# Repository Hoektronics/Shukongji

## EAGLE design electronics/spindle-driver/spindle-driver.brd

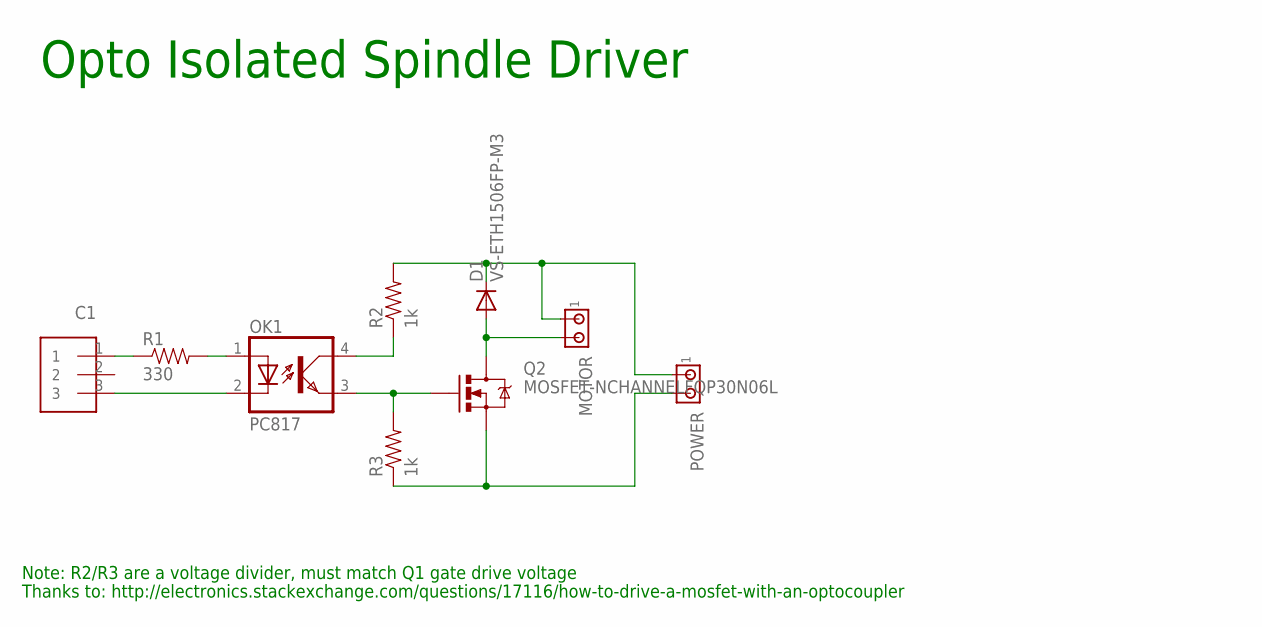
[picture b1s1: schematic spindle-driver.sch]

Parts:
C1: CONN-3XH-3; XH-3
D1: VS-ETH1506FP-M3; SMB
MOTOR: MTA02-156; 1X2MTA
OK1: PC817; DIL04
POWER: MTA02-156; 1X2MTA
Q2: MOSFET-NCHANNELFQP30N06L; TO220V
R1: 330; 0805-RC
R2, R3: 1k; 0805-RC

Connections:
unnamed: C1.3, OK1.2 (C)
unnamed: OK1.1 (A), R1.2
unnamed: C1.1, R1.1
unnamed: D1.C, MOTOR.1, POWER.1, R2.2
unnamed: OK1.4 (COL), R2.1
unnamed: OK1.3 (EMIT), Q2.1 (G), R3.2
unnamed: POWER.2, Q2.3 (S), R3.1
unnamed: D1.A, MOTOR.2, Q2.2 (D)

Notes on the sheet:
Thanks to: http://electronics.stackexchange.com/questions/17116/how-to-drive-a-mosfet-with-an-optocoupler
Note: R2/R3 are a voltage divider, must match Q1 gate drive voltage
Opto Isolated Spindle Driver

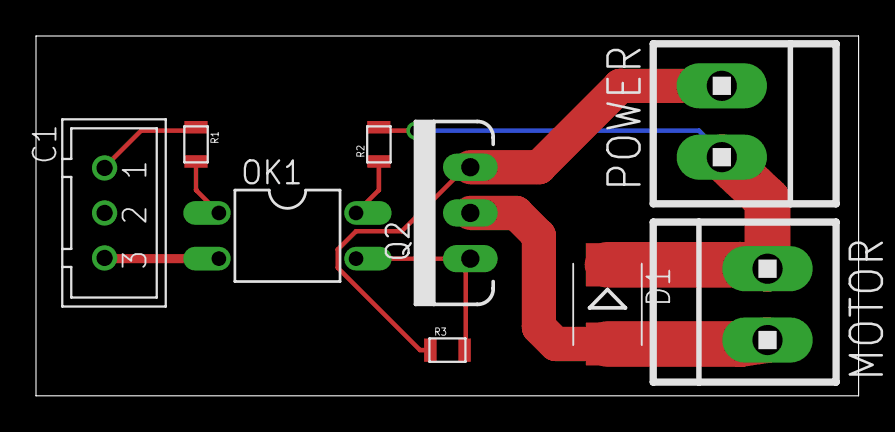
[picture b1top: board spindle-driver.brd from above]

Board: 2 copper layers, 45.7 x 20.0 mm, 9 parts (0 on the bottom side), 8 nets.

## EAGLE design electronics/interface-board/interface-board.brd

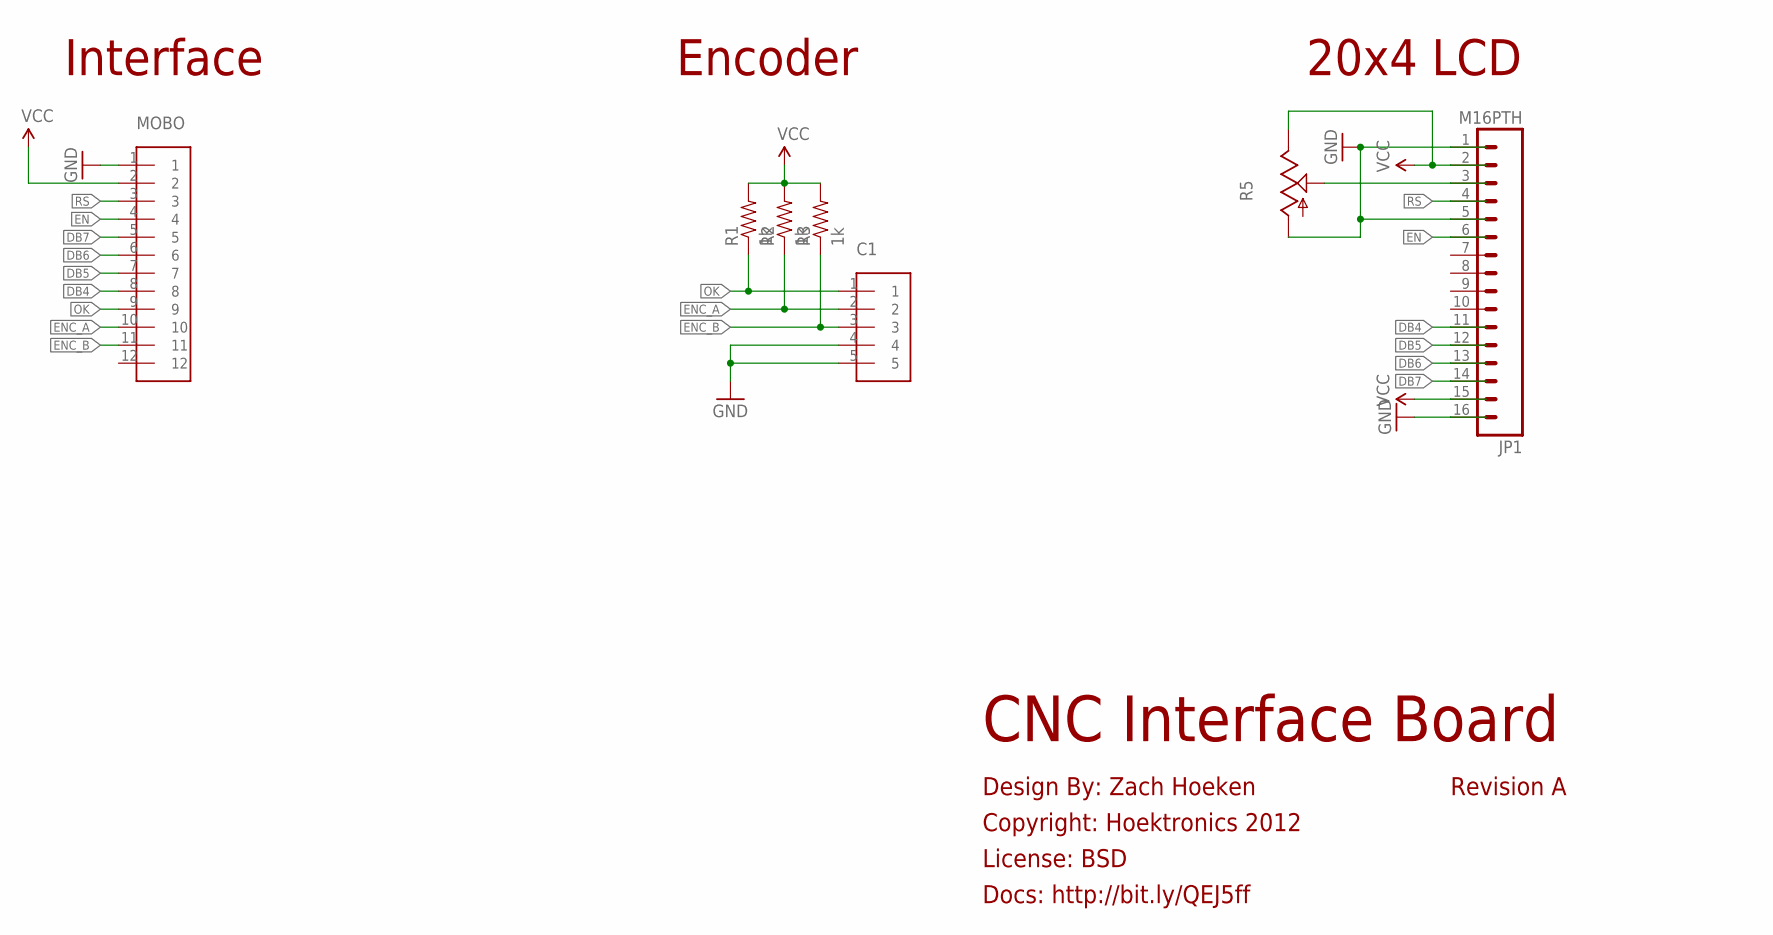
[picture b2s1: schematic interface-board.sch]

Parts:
C1: CONN-5; XH-5
JP1: M16PTH; 1X16
MOBO: CONN-12; XH-12
R1, R2, R3: 1k; 0805-RC
R5: TRIM_US-B25P; B25P

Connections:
DB4: JP1.11, MOBO.8
DB5: JP1.12, MOBO.7
DB6: JP1.13, MOBO.6
DB7: JP1.14, MOBO.5
EN: JP1.6, MOBO.4
ENC_A: C1.2, MOBO.10, R2.1
ENC_B: C1.3, MOBO.11, R3.1
GND: C1.4, C1.5, JP1.1, JP1.5, JP1.16, MOBO.1, R5.A
unnamed: JP1.3, R5.S
OK: C1.1, MOBO.9, R1.1
RS: JP1.4, MOBO.3
VCC: JP1.2, JP1.15, MOBO.2, R1.2, R2.2, R3.2, R5.E

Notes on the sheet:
CNC Interface Board
Docs: http://bit.ly/QEJ5ff
License: BSD
Copyright: Hoektronics 2012
Design By: Zach Hoeken
20x4 LCD
Revision A
Interface
Encoder

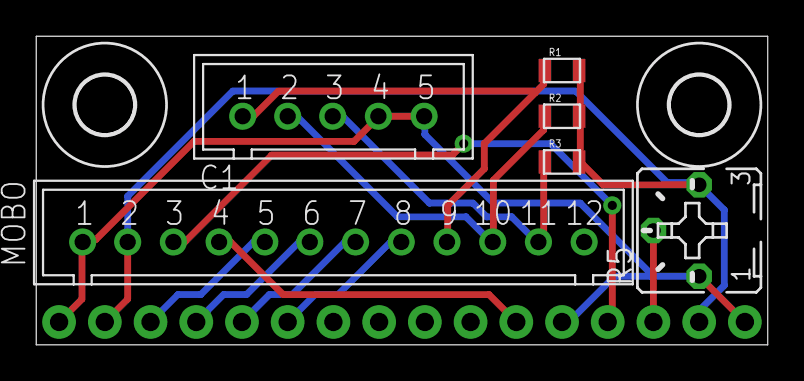
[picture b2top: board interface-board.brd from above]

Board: 2 copper layers, 40.6 x 17.1 mm, 9 parts (1 on the bottom side), 12 nets.

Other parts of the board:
U$1, U$2: 3,2

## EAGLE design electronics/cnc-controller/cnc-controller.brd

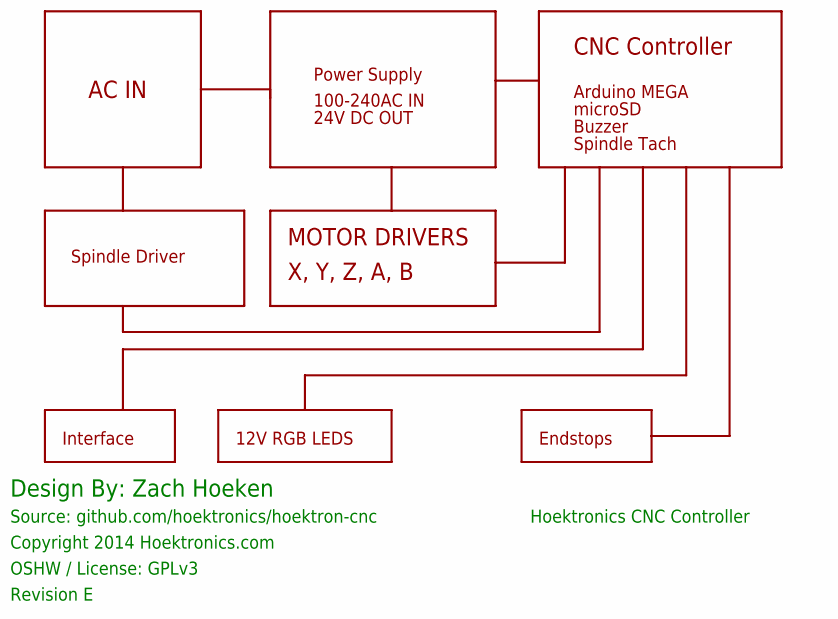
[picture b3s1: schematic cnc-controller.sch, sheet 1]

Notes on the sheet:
Hoektronics CNC Controller
Design By: Zach Hoeken
Source: github.com/hoektronics/hoektron-cnc
Copyright 2014 Hoektronics.com
Power Supply
X, Y, Z, A, B
CNC Controller
microSD
Endstops
Buzzer
OSHW / License: GPLv3
12V RGB LEDS
24V DC OUT
Interface
Revision E
Arduino MEGA
100-240AC IN
AC IN
MOTOR DRIVERS
Spindle Tach
Spindle Driver

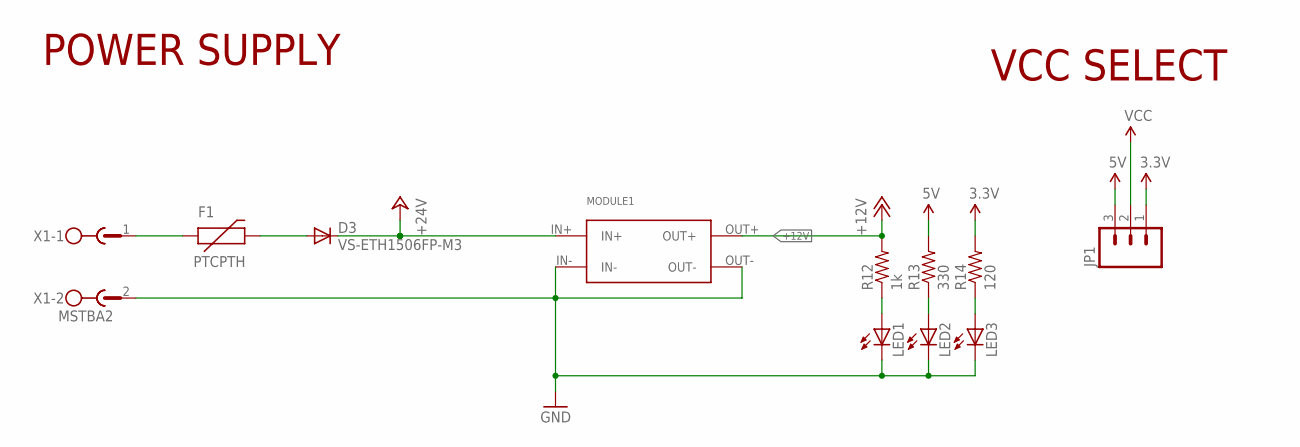
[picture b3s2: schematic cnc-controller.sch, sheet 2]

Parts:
D3: VS-ETH1506FP-M3; SMB
F1: PTCPTH; PTC
JP1: M03PTH; 1X03
LED1, LED2, LED3: LED0805; 0805-LED
MODULE1: DC-DC-CONVERTER; DC-DC-MODULE
R12: 1k; 0603-RC
R13: 330; 0603-RC
R14: 120; 0603-RC
X1: MSTBA2

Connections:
3.3V: JP1.1, R14.2; also elsewhere on the board
5V: JP1.3, R13.2; also elsewhere on the board
+12V: MODULE1.OUT+, R12.2; also elsewhere on the board
+24V: D3.C, MODULE1.IN+
GND: LED1.C, LED2.C, LED3.C, MODULE1.IN-, MODULE1.OUT-, X1.2; also elsewhere on the board
unnamed: LED1.A, R12.1
unnamed: D3.A, F1.P$2 (2)
unnamed: LED2.A, R13.1
unnamed: LED3.A, R14.1
PRE24: F1.P$1 (1), X1.1
VCC: JP1.2; also elsewhere on the board

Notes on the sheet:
POWER SUPPLY
VCC SELECT

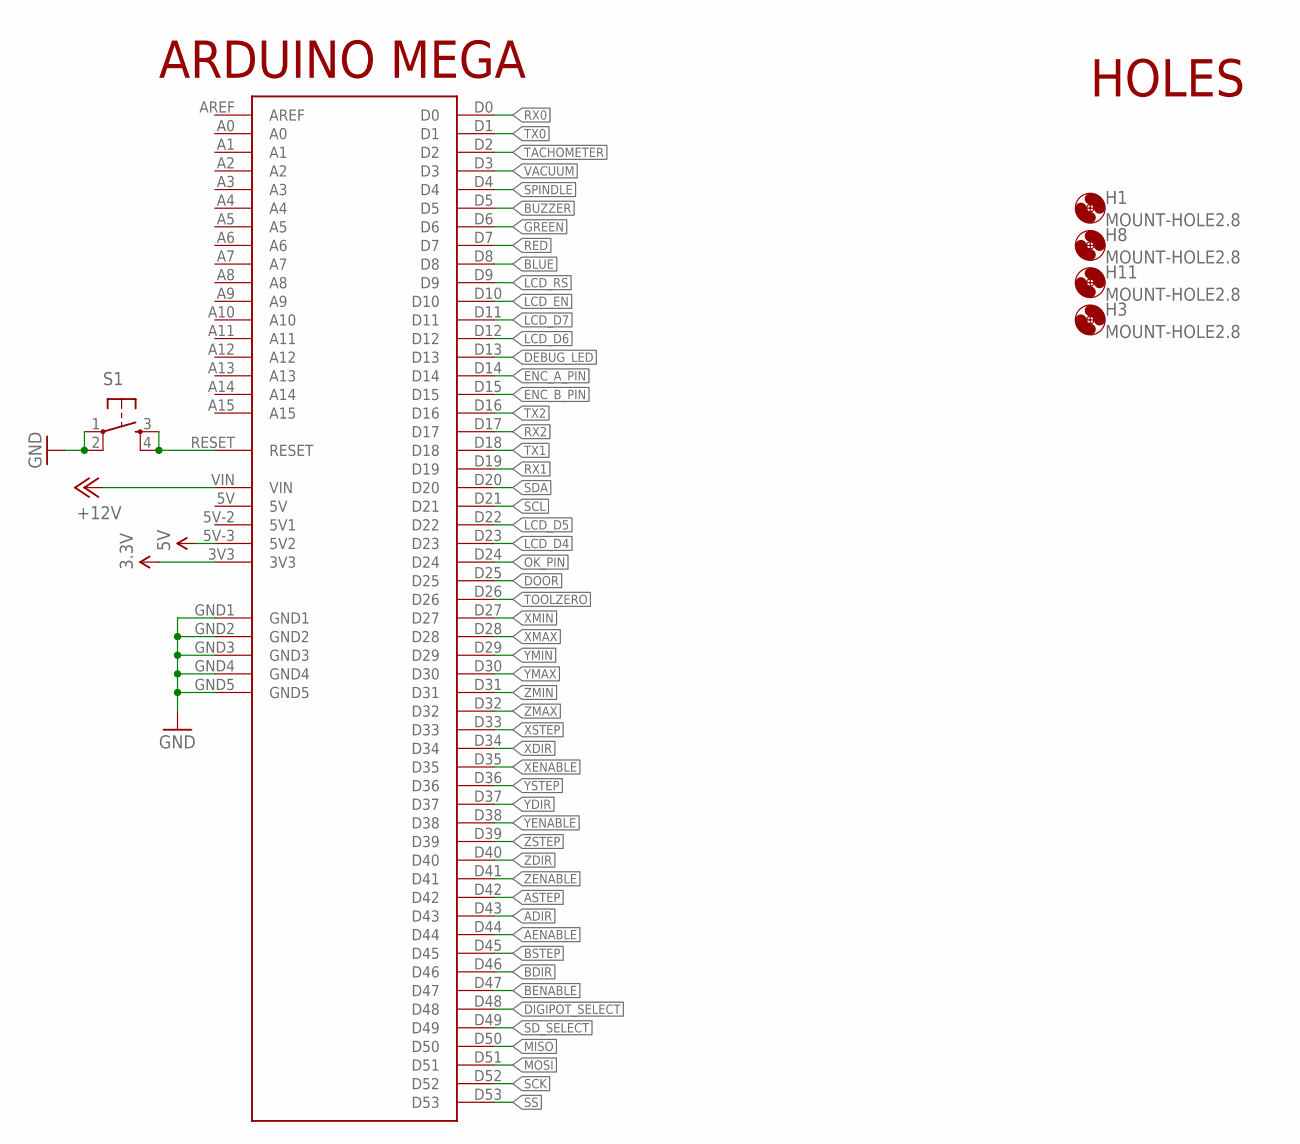
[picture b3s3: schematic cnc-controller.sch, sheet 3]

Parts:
H1, H3, H8, H11: MOUNT-HOLE2.8; 2,8
S1: TAC_SWITCHSMD; TACTILE_SWITCH_SMD
U$1: ARDUINO-MEGA

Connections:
3.3V: U$1.3V3; also elsewhere on the board
5V: U$1.5V-3 (5V2); also elsewhere on the board
+12V: U$1.VIN; also elsewhere on the board
ADIR: U$1.D43; also elsewhere on the board
AENABLE: U$1.D44; also elsewhere on the board
ASTEP: U$1.D42; also elsewhere on the board
BDIR: U$1.D46; also elsewhere on the board
BENABLE: U$1.D47; also elsewhere on the board
BLUE: U$1.D8; also elsewhere on the board
BSTEP: U$1.D45; also elsewhere on the board
BUZZER: U$1.D5; also elsewhere on the board
DEBUG_LED: U$1.D13
DIGIPOT_SELECT: U$1.D48
DOOR: U$1.D25; also elsewhere on the board
ENC_A_PIN: U$1.D14; also elsewhere on the board
ENC_B_PIN: U$1.D15; also elsewhere on the board
GND: S1.1, S1.2, U$1.GND1, U$1.GND2, U$1.GND3, U$1.GND4, U$1.GND5; also elsewhere on the board
GREEN: U$1.D6; also elsewhere on the board
LCD_D4: U$1.D23; also elsewhere on the board
LCD_D5: U$1.D22; also elsewhere on the board
LCD_D6: U$1.D12; also elsewhere on the board
LCD_D7: U$1.D11; also elsewhere on the board
LCD_EN: U$1.D10; also elsewhere on the board
LCD_RS: U$1.D9; also elsewhere on the board
MISO: U$1.D50; also elsewhere on the board
MOSI: U$1.D51; also elsewhere on the board
unnamed: S1.3, S1.4, U$1.RESET
OK_PIN: U$1.D24; also elsewhere on the board
RED: U$1.D7; also elsewhere on the board
RX0: U$1.D0
RX1: U$1.D19; also elsewhere on the board
RX2: U$1.D17; also elsewhere on the board
SCK: U$1.D52; also elsewhere on the board
SCL: U$1.D21; also elsewhere on the board
SDA: U$1.D20; also elsewhere on the board
SD_SELECT: U$1.D49; also elsewhere on the board
SPINDLE: U$1.D4; also elsewhere on the board
SS: U$1.D53; also elsewhere on the board
TACHOMETER: U$1.D2; also elsewhere on the board
TOOLZERO: U$1.D26; also elsewhere on the board
TX0: U$1.D1
TX1: U$1.D18; also elsewhere on the board
TX2: U$1.D16; also elsewhere on the board
VACUUM: U$1.D3; also elsewhere on the board
XDIR: U$1.D34; also elsewhere on the board
XENABLE: U$1.D35; also elsewhere on the board
XMAX: U$1.D28; also elsewhere on the board
XMIN: U$1.D27; also elsewhere on the board
XSTEP: U$1.D33; also elsewhere on the board
YDIR: U$1.D37; also elsewhere on the board
YENABLE: U$1.D38; also elsewhere on the board
YMAX: U$1.D30; also elsewhere on the board
YMIN: U$1.D29; also elsewhere on the board
YSTEP: U$1.D36; also elsewhere on the board
ZDIR: U$1.D40; also elsewhere on the board
ZENABLE: U$1.D41; also elsewhere on the board
ZMAX: U$1.D32; also elsewhere on the board
ZMIN: U$1.D31; also elsewhere on the board
ZSTEP: U$1.D39; also elsewhere on the board

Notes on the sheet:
ARDUINO MEGA
HOLES

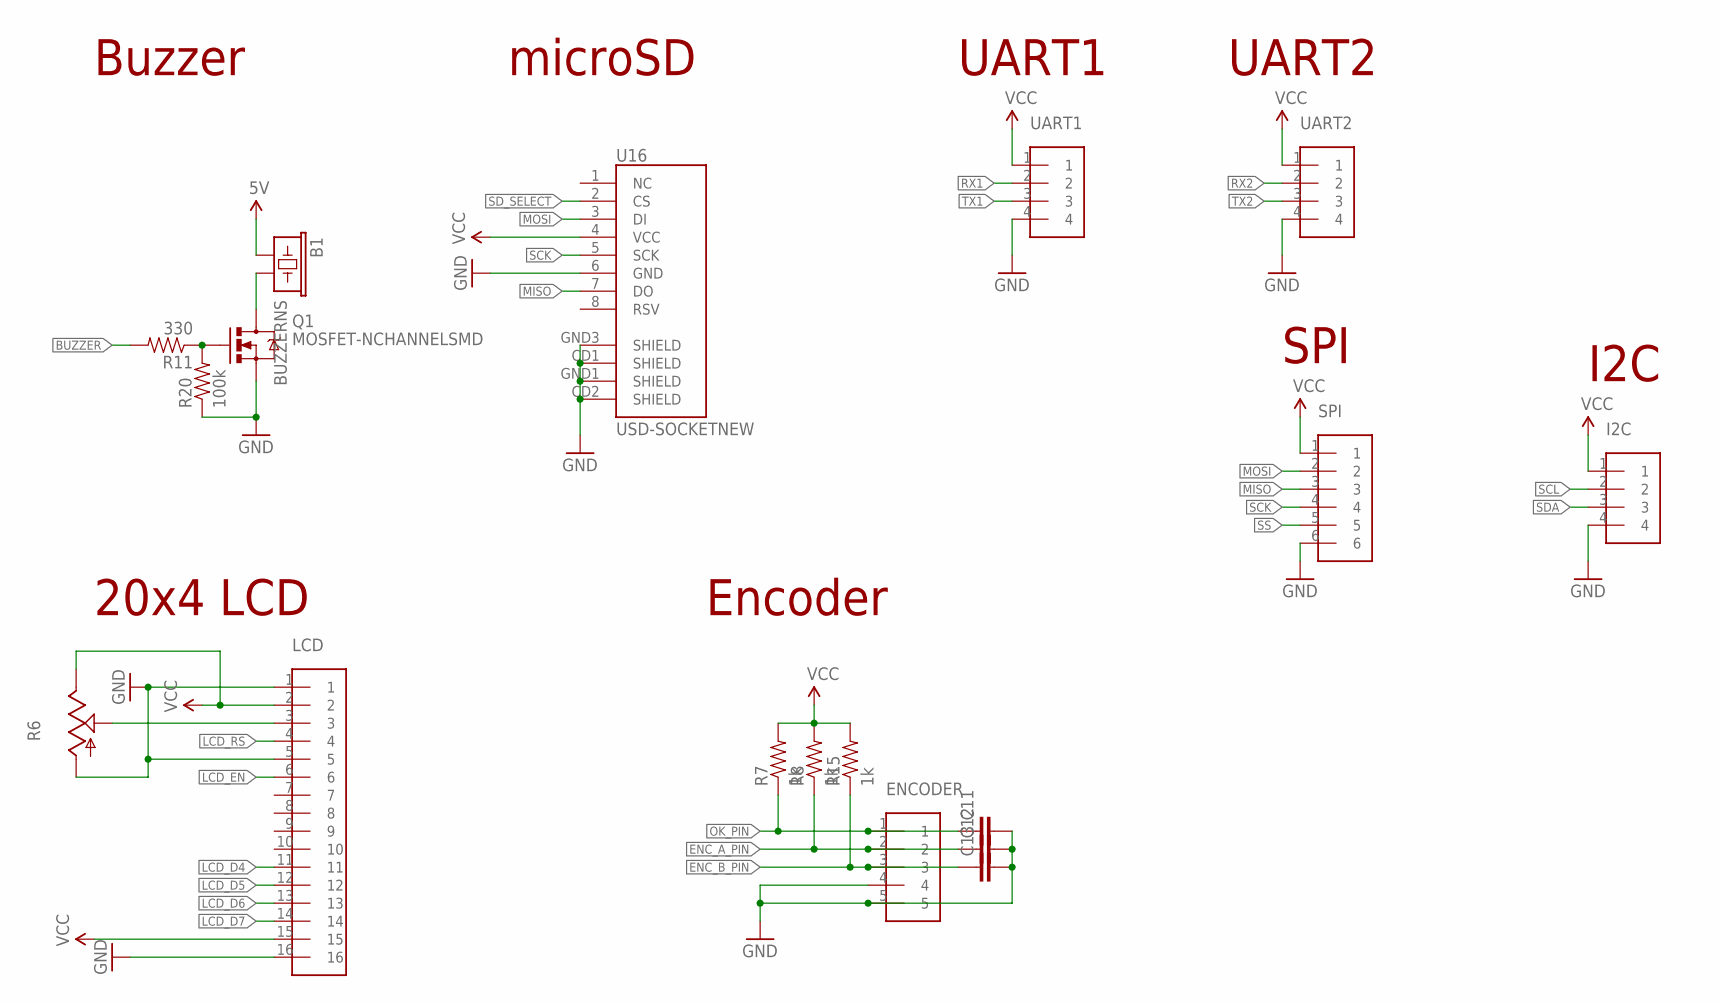
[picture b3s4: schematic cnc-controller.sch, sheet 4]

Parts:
B1: BUZZERNS; BUZZER-12MM-NS
C11, C12, C13: CAPACITOR0805; 0805-RC
ENCODER: CONN-5; XH-5
I2C: CONN-4; XH-4
LCD: CONN-16; XH-16
Q1: MOSFET-NCHANNELSMD; SOT23-3
R6: TRIM_US-B25P; B25P
R7, R8, R15: 1k; 0805-RC
R11: 330; 0603-RC
R20: 100k; 0603-RC
SPI: CONN-6; XH-6
U16: USD-SOCKETNEW; MICRO-SD-SOCKET-PP
UART1, UART2: CONN-4; XH-4

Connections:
5V: B1.+ (1); also elsewhere on the board
BUZZER: R11.2; also elsewhere on the board
ENC_A_PIN: C12.1, ENCODER.2, R8.1; also elsewhere on the board
ENC_B_PIN: C13.1, ENCODER.3, R15.1; also elsewhere on the board
GND: C11.2, C12.2, C13.2, ENCODER.4, ENCODER.5, I2C.4, LCD.1, LCD.5, LCD.16, Q1.2 (S), R6.A, R20.1, SPI.6, U16.6 (GND), U16.CD1 (SHIELD), U16.CD2 (SHIELD), U16.GND1 (SHIELD), U16.GND3 (SHIELD), UART1.4, UART2.4; also elsewhere on the board
LCD_D4: LCD.11; also elsewhere on the board
LCD_D5: LCD.12; also elsewhere on the board
LCD_D6: LCD.13; also elsewhere on the board
LCD_D7: LCD.14; also elsewhere on the board
LCD_EN: LCD.6; also elsewhere on the board
LCD_RS: LCD.4; also elsewhere on the board
MISO: SPI.3, U16.7 (DO); also elsewhere on the board
MOSI: SPI.2, U16.3 (DI); also elsewhere on the board
unnamed: LCD.3, R6.S
unnamed: Q1.1 (G), R11.1, R20.2
unnamed: B1.- (2), Q1.3 (D)
OK_PIN: C11.1, ENCODER.1, R7.1; also elsewhere on the board
RX1: UART1.2; also elsewhere on the board
RX2: UART2.2; also elsewhere on the board
SCK: SPI.4, U16.5 (SCK); also elsewhere on the board
SCL: I2C.2; also elsewhere on the board
SDA: I2C.3; also elsewhere on the board
SD_SELECT: U16.2 (CS); also elsewhere on the board
SS: SPI.5; also elsewhere on the board
TX1: UART1.3; also elsewhere on the board
TX2: UART2.3; also elsewhere on the board
VCC: I2C.1, LCD.2, LCD.15, R6.E, R7.2, R8.2, R15.2, SPI.1, U16.4 (VCC), UART1.1, UART2.1; also elsewhere on the board

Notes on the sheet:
Buzzer
microSD
SPI
I2C
UART2
UART1
20x4 LCD
Encoder

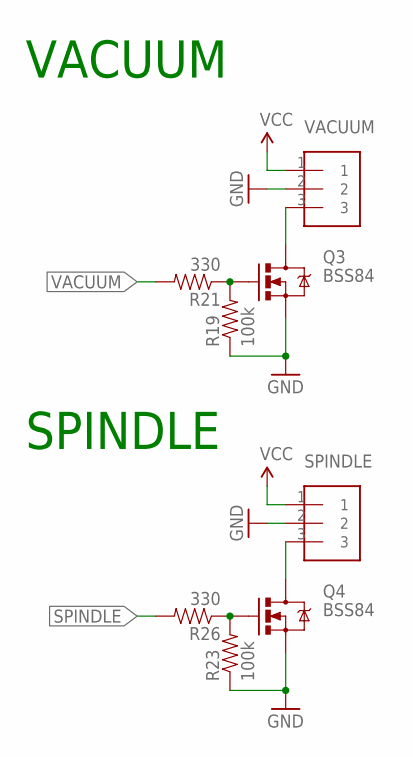
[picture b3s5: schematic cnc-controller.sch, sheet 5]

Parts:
Q3, Q4: BSS84; SOT23-3
R19, R23: 100k; 0603-RC
R21, R26: 330; 0603-RC
SPINDLE: CONN-3XH-3; XH-3
VACUUM: CONN-3XH-3; XH-3

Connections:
GND: Q3.2 (S), Q4.2 (S), R19.1, R23.1, SPINDLE.2, VACUUM.2; also elsewhere on the board
unnamed: Q3.1 (G), R19.2, R21.1
unnamed: Q4.1 (G), R23.2, R26.1
unnamed: Q3.3 (D), VACUUM.3
unnamed: Q4.3 (D), SPINDLE.3
SPINDLE: R26.2; also elsewhere on the board
VACUUM: R21.2; also elsewhere on the board
VCC: SPINDLE.1, VACUUM.1; also elsewhere on the board

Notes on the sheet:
VACUUM
SPINDLE

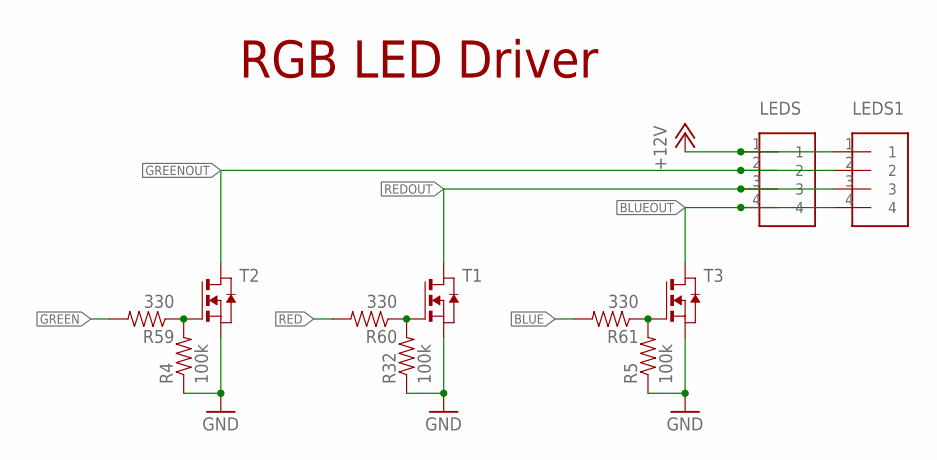
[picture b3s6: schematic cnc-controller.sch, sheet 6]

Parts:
LEDS, LEDS1: CONN-4; XH-4
R4, R5, R32: 100k; 0603-RC
R59, R60, R61: 330; 0603-RC
T1, T2, T3: NMOSSOT89; SOT89

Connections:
+12V: LEDS.1, LEDS1.1; also elsewhere on the board
BLUE: R61.2; also elsewhere on the board
BLUEOUT: LEDS.4, LEDS1.4, T3.2 (D)
GND: R4.1, R5.1, R32.1, T1.3 (S), T2.3 (S), T3.3 (S); also elsewhere on the board
GREEN: R59.2; also elsewhere on the board
GREENOUT: LEDS.2, LEDS1.2, T2.2 (D)
unnamed: R32.2, R60.1, T1.1 (G)
unnamed: R4.2, R59.1, T2.1 (G)
unnamed: R5.2, R61.1, T3.1 (G)
RED: R60.2; also elsewhere on the board
REDOUT: LEDS.3, LEDS1.3, T1.2 (D)

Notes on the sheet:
RGB LED Driver

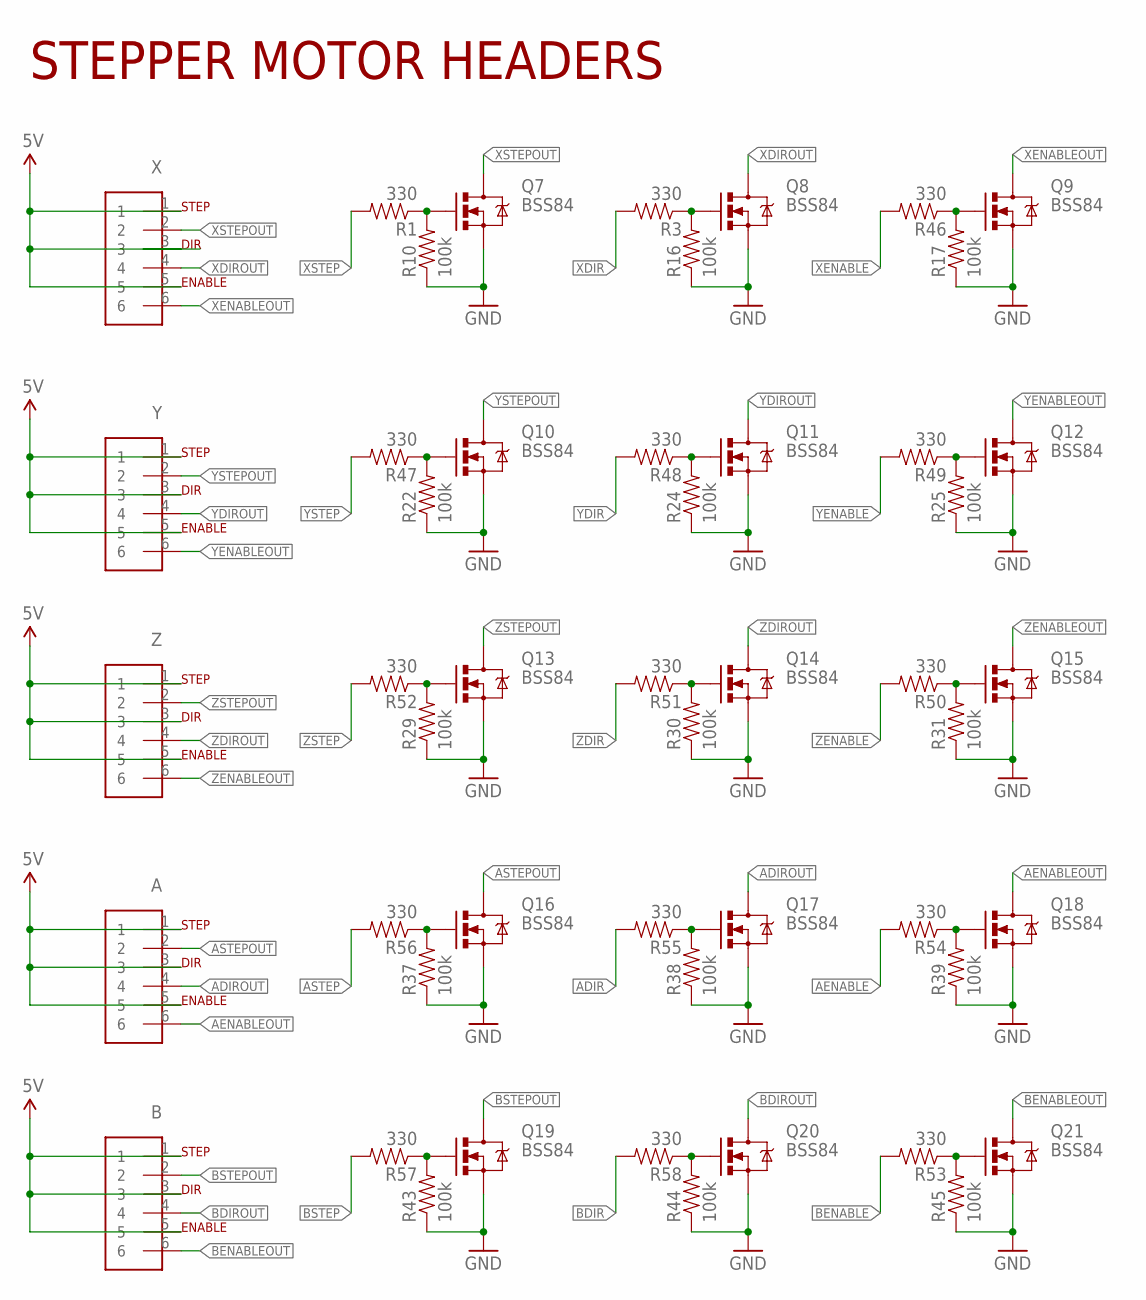
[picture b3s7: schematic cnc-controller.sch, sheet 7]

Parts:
A: CONN-6; XH-6
B: CONN-6; XH-6
Q7, Q8, Q9, Q10, Q11, Q12, Q13, Q14, Q15, Q16, Q17, Q18, Q19, Q20, Q21: BSS84; SOT23-3
R1, R3, R46, R47, R48, R49, R50, R51, R52, R53, R54, R55, R56, R57, R58: 330; 0603-RC
R10, R16, R17, R22, R24, R25, R29, R30, R31, R37, R38, R39, R43, R44, R45: 100k; 0603-RC
X: CONN-6; XH-6
Y: CONN-6; XH-6
Z: CONN-6; XH-6

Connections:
5V: A.1, A.3, A.5, B.1, B.3, B.5, X.1, X.3, X.5, Y.1, Y.3, Y.5, Z.1, Z.3, Z.5; also elsewhere on the board
ADIR: R55.2; also elsewhere on the board
ADIROUT: A.4, Q17.3 (D)
AENABLE: R54.2; also elsewhere on the board
AENABLEOUT: A.6, Q18.3 (D)
ASTEP: R56.2; also elsewhere on the board
ASTEPOUT: A.2, Q16.3 (D)
BDIR: R58.2; also elsewhere on the board
BDIROUT: B.4, Q20.3 (D)
BENABLE: R53.2; also elsewhere on the board
BENABLEOUT: B.6, Q21.3 (D)
BSTEP: R57.2; also elsewhere on the board
BSTEPOUT: B.2, Q19.3 (D)
GND: Q7.2 (S), Q8.2 (S), Q9.2 (S), Q10.2 (S), Q11.2 (S), Q12.2 (S), Q13.2 (S), Q14.2 (S), Q15.2 (S), Q16.2 (S), Q17.2 (S), Q18.2 (S), Q19.2 (S), Q20.2 (S), Q21.2 (S), R10.1, R16.1, R17.1, R22.1, R24.1, R25.1, R29.1, R30.1, R31.1, R37.1, R38.1, R39.1, R43.1, R44.1, R45.1; also elsewhere on the board
unnamed: Q10.1 (G), R22.2, R47.1
unnamed: Q19.1 (G), R43.2, R57.1
unnamed: Q20.1 (G), R44.2, R58.1
unnamed: Q21.1 (G), R45.2, R53.1
unnamed: Q16.1 (G), R37.2, R56.1
unnamed: Q17.1 (G), R38.2, R55.1
unnamed: Q18.1 (G), R39.2, R54.1
unnamed: Q11.1 (G), R24.2, R48.1
unnamed: Q12.1 (G), R25.2, R49.1
unnamed: Q15.1 (G), R31.2, R50.1
unnamed: Q14.1 (G), R30.2, R51.1
unnamed: Q13.1 (G), R29.2, R52.1
XDIR: R3.2; also elsewhere on the board
XDIRIN: Q8.1 (G), R3.1, R16.2
XDIROUT: Q8.3 (D), X.4
XENABLE: R46.2; also elsewhere on the board
XENABLEIN: Q9.1 (G), R17.2, R46.1
XENABLEOUT: Q9.3 (D), X.6
XSTEP: R1.2; also elsewhere on the board
XSTEPIN: Q7.1 (G), R1.1, R10.2
XSTEPOUT: Q7.3 (D), X.2
YDIR: R48.2; also elsewhere on the board
YDIROUT: Q11.3 (D), Y.4
YENABLE: R49.2; also elsewhere on the board
YENABLEOUT: Q12.3 (D), Y.6
YSTEP: R47.2; also elsewhere on the board
YSTEPOUT: Q10.3 (D), Y.2
ZDIR: R51.2; also elsewhere on the board
ZDIROUT: Q14.3 (D), Z.4
ZENABLE: R50.2; also elsewhere on the board
ZENABLEOUT: Q15.3 (D), Z.6
ZSTEP: R52.2; also elsewhere on the board
ZSTEPOUT: Q13.3 (D), Z.2

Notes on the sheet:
STEP
DIR
ENABLE
STEPPER MOTOR HEADERS

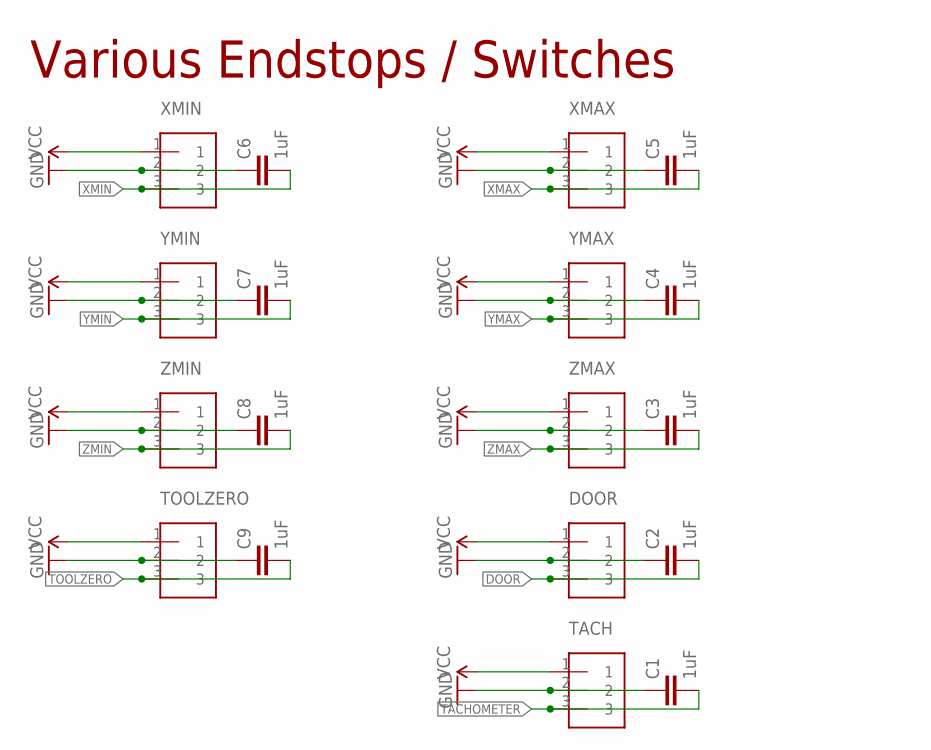
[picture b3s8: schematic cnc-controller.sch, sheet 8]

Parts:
C1, C2, C3, C4, C5, C6, C7, C8, C9: 1uF; 0603-RC
DOOR: CONN-3XH-3; XH-3
TACH: CONN-3XH-3; XH-3
TOOLZERO: CONN-3XH-3; XH-3
XMAX: CONN-3XH-3; XH-3
XMIN: CONN-3XH-3; XH-3
YMAX: CONN-3XH-3; XH-3
YMIN: CONN-3XH-3; XH-3
ZMAX: CONN-3XH-3; XH-3
ZMIN: CONN-3XH-3; XH-3

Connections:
DOOR: C2.2, DOOR.3; also elsewhere on the board
GND: C1.1, C2.1, C3.1, C4.1, C5.1, C6.1, C7.1, C8.1, C9.1, DOOR.2, TACH.2, TOOLZERO.2, XMAX.2, XMIN.2, YMAX.2, YMIN.2, ZMAX.2, ZMIN.2; also elsewhere on the board
TACHOMETER: C1.2, TACH.3; also elsewhere on the board
TOOLZERO: C9.2, TOOLZERO.3; also elsewhere on the board
VCC: DOOR.1, TACH.1, TOOLZERO.1, XMAX.1, XMIN.1, YMAX.1, YMIN.1, ZMAX.1, ZMIN.1; also elsewhere on the board
XMAX: C5.2, XMAX.3; also elsewhere on the board
XMIN: C6.2, XMIN.3; also elsewhere on the board
YMAX: C4.2, YMAX.3; also elsewhere on the board
YMIN: C7.2, YMIN.3; also elsewhere on the board
ZMAX: C3.2, ZMAX.3; also elsewhere on the board
ZMIN: C8.2, ZMIN.3; also elsewhere on the board

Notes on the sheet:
Various Endstops / Switches

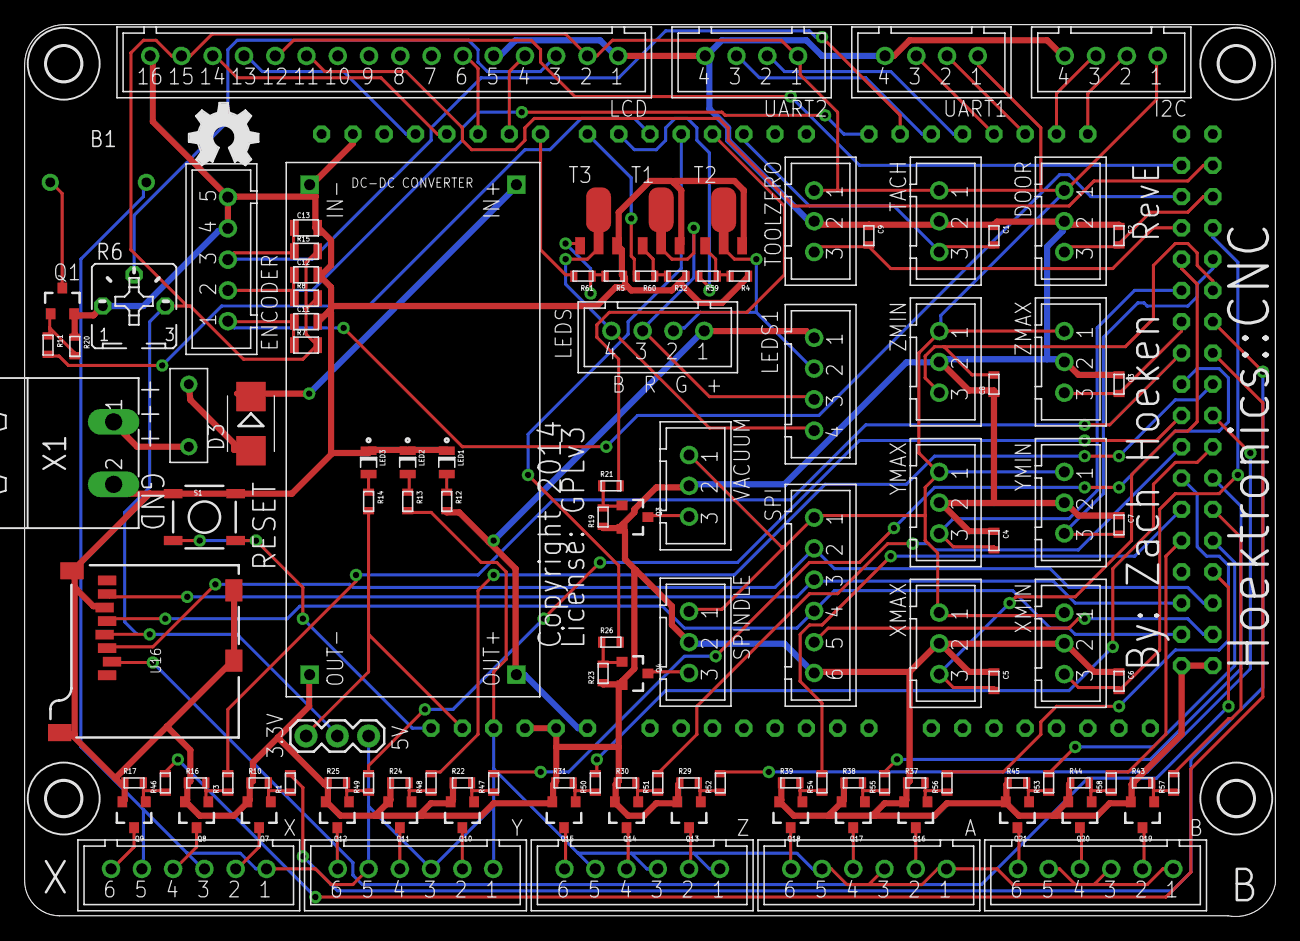
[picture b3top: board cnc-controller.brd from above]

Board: 2 copper layers, 101.6 x 72.4 mm, 123 parts (0 on the bottom side), 105 nets.

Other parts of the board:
U$12: OSHW_FILLX200_NOTEXT

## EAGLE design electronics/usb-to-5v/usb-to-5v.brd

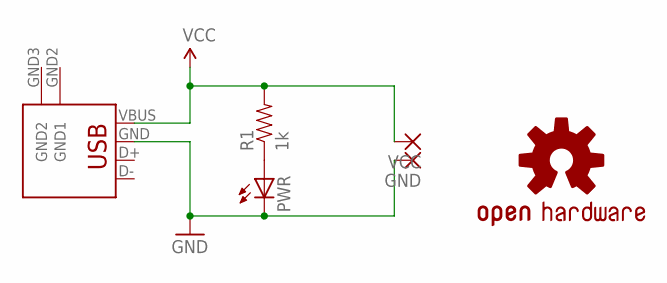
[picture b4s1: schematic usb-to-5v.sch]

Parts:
GND: 1,6/0,9
JP1: USB-A-H
LOGO1: OSHW-LOGOS; OSHW-LOGO-S
PWR: LED0805; 0805-LED
R1: 1k; 0805-RC
VCC: 1,6/0,9

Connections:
GND: GND.1, JP1.GND (VBUS), PWR.C
unnamed: PWR.A, R1.1
VCC: JP1.VBUS (GND), R1.2, VCC.1

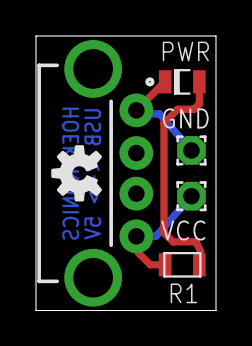
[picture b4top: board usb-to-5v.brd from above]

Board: 2 copper layers, 10.0 x 15.2 mm, 6 parts (0 on the bottom side), 3 nets.

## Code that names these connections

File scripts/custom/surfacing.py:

import math
import argparse

def main():
  parser = argparse.ArgumentParser(description='Surfacing Script')
  parser.add_argument('-x','--xmax', help='Maximum available X area in millimeters', required=False, default=180)
  parser.add_argument('-y','--ymax', help='Maximum available Y area in millimeters', required=False, default=190)
  parser.add_argument('-t','--toolsize', help='Diameter of the tool in millimeters', required=False, default=4)
  parser.add_argument('-m','--millrate', help='Milling feedrate in mm/min', required=False, default=800)
  parser.add_argument('-p','--plungerate', help='Plunge feedreate in mm/min', required=False, default=400)
  parser.add_argument('-r','--rpm', help='Milling tool RPM', required=False, default=5000)
  parser.add_argument('-d','--depth', help='Depth in millimeters', required=False, default=0.25)
  parser.add_argument('-i','--increment', help='Increment in millimeters', required=False, default=0.25)
  parser.add_argument('--home', help='Home or not home', required=False, default=False)
  parser.add_argument('-v', '--version', action='version', version='%(prog)s 1.0')

  results = parser.parse_args()
  
  #configuration
  xmin = 0
  xmax = float(results.xmax)
  ymin = 0
  ymax = float(results.ymax)
  toolsize = float(results.toolsize)
  rpm = float(results.rpm)
  pathsize = toolsize - 1.0
  millFeedrate = float(results.millrate)
  plungeFeedrate = float(results.plungerate)
  surfaceDepth = math.fabs(float(results.depth))
  increment = math.fabs(float(results.increment))
  
  #initialize
  cnc = CNCMachine()
  cnc.start()
  if results.home:
    cnc.home(z=True)
    cnc.home(x=True, y=True)
    cnc.setPosition(xmax+0.5, -0.5, 55.5) #we home to xmax, ymin, zmax w/ 0.5mm of clearance.
    cnc.goto(x=0, y=0, feedrate=0) #max speed move
  else:
    cnc.setPosition(0,0,0) #start at 0,0,0
    
  cnc.motorsOff()
  cnc.confirm("Adjust bit to 6mm")
  cnc.setPosition(0, 0, 6)
  cnc.spindleOn(rpm)


  #do it multiple times
  for z in range(int(math.floor(surfaceDepth / increment))):
    #how deep this pass?
    depth = -increment * (z+1)

    #mill a big square
    cnc.goto(x=0, y=0, z=depth, feedrate=plungeFeedrate)
    cnc.goto(x=0, y=ymax, feedrate=millFeedrate)
    cnc.goto(x=xmax, y=ymax, feedrate=millFeedrate)
    cnc.goto(x=xmax, y=0, feedrate=millFeedrate)

    #surface milling
    for y in range(0, int(math.ceil(ymax/pathsize))):
      ypos = y * pathsize
      cnc.goto(y=ypos, feedrate=millFeedrate)
      if cnc.x == xmin:
        cnc.goto(x = xmax, y = ypos, feedrate=millFeedrate)
      else:
        cnc.goto(x = xmin, y = ypos, feedrate=millFeedrate)

    #back to our origin, safely
    cnc.goto(z=6, feedrate=0)
    cnc.goto(x=0, y=0, feedrate=0)
  
  #we're done!
  cnc.end()

class Endmill():
  def __init__(self, width):
    self.width = width

class Machine():
  
  def __init__(self):
    self.x = 0;
    self.y = 0;
    self.z = 0;
    self.feedrate = 0;
    
  def goto(self, x=None, y=None, z=None, feedrate=None):
    if feedrate is not None:
      self.feedrate = feedrate;
    if x is not None:
      self.x = x
    if y is not None:
      self.y = y
    if z is not None:
      self.z = z

    if feedrate <= 0:
      str = "G0 X%0.4f Y%0.4f Z%0.4f" % (self.x, self.y, self.z)
    else:
      str = "G1 X%0.4f Y%0.4f Z%0.4f F%0.4f" % (self.x, self.y, self.z, self.feedrate)

    self.output(str);
  
  def wait(self, time):
    str = "G4 S%0.4f" % time
    self.output(str);
  
  def home(self, x=None, y=None, z=None):
    str = "G28 "
    if x is not None:
      str += "X"
    if y is not None:
      str += "Y"
    if z is not None:
      str += "Z"
    
    self.output(str)
  
  def setPosition(self, x=None, y=None, z=None):
    if x is not None:
      self.x = x;
    if y is not None:
      self.y = y;
    if z is not None:
      self.z = z;
      
    str = "G92 X%0.4f Y%0.4f Z%0.4f" % (self.x, self.y, self.z)
    self.output(str)
    
  def confirm(self, message):
    str = "M1 (%s)" % message
    self.output(str)

  def motorsOn(self):
    self.output("M17 (Motors On)")

  def motorsOff(self):
    self.output("M18 (Motors Off)")

  def beep(self, frequency, duration):
    self.output("M300 S%d P%d" % (frequency, duration))

  def ledColor(self, red, green, blue):
    self.output("M420 R%d E%d B%d" % (red, green, blue))
    
  def output(self, str):
    print str;
    
class CNCMachine(Machine):
  def start(self):
    self.ledColor(255, 255, 255)

  def end(self):
    self.spindleOff()
    self.vacuumOff()
    self.coolantOff()
    self.ledColor(0, 0, 255)
    self.beep(600, 1000)
    self.motorsOff()

  def spindleOn(self, rpm):
    self.output("M3 S%s (Spindle On)" % rpm)

  def spindleOff(self):
    self.output("M5 (Spindle Off)")

  def coolantOn(self):
    self.output("M7 (Coolant On)")

  def coolantOff(self):
    self.output("M9 (Coolant Off)")

  def vacuumOn(self):
    self.output("M10 (Vacuum On)")

  def vacuumOff(self):
    self.output("M11 (Vacuum Off)")
        
if __name__ == '__main__':
  main()

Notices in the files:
parts and their libraries:
SparkFun-Aesthetics: Licensing: CC v3.0 Share-Alike You are welcome to use this library for commercial purposes.
